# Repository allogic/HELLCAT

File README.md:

# HELLCAT
4-channel DRV8825 stepper motor driver.

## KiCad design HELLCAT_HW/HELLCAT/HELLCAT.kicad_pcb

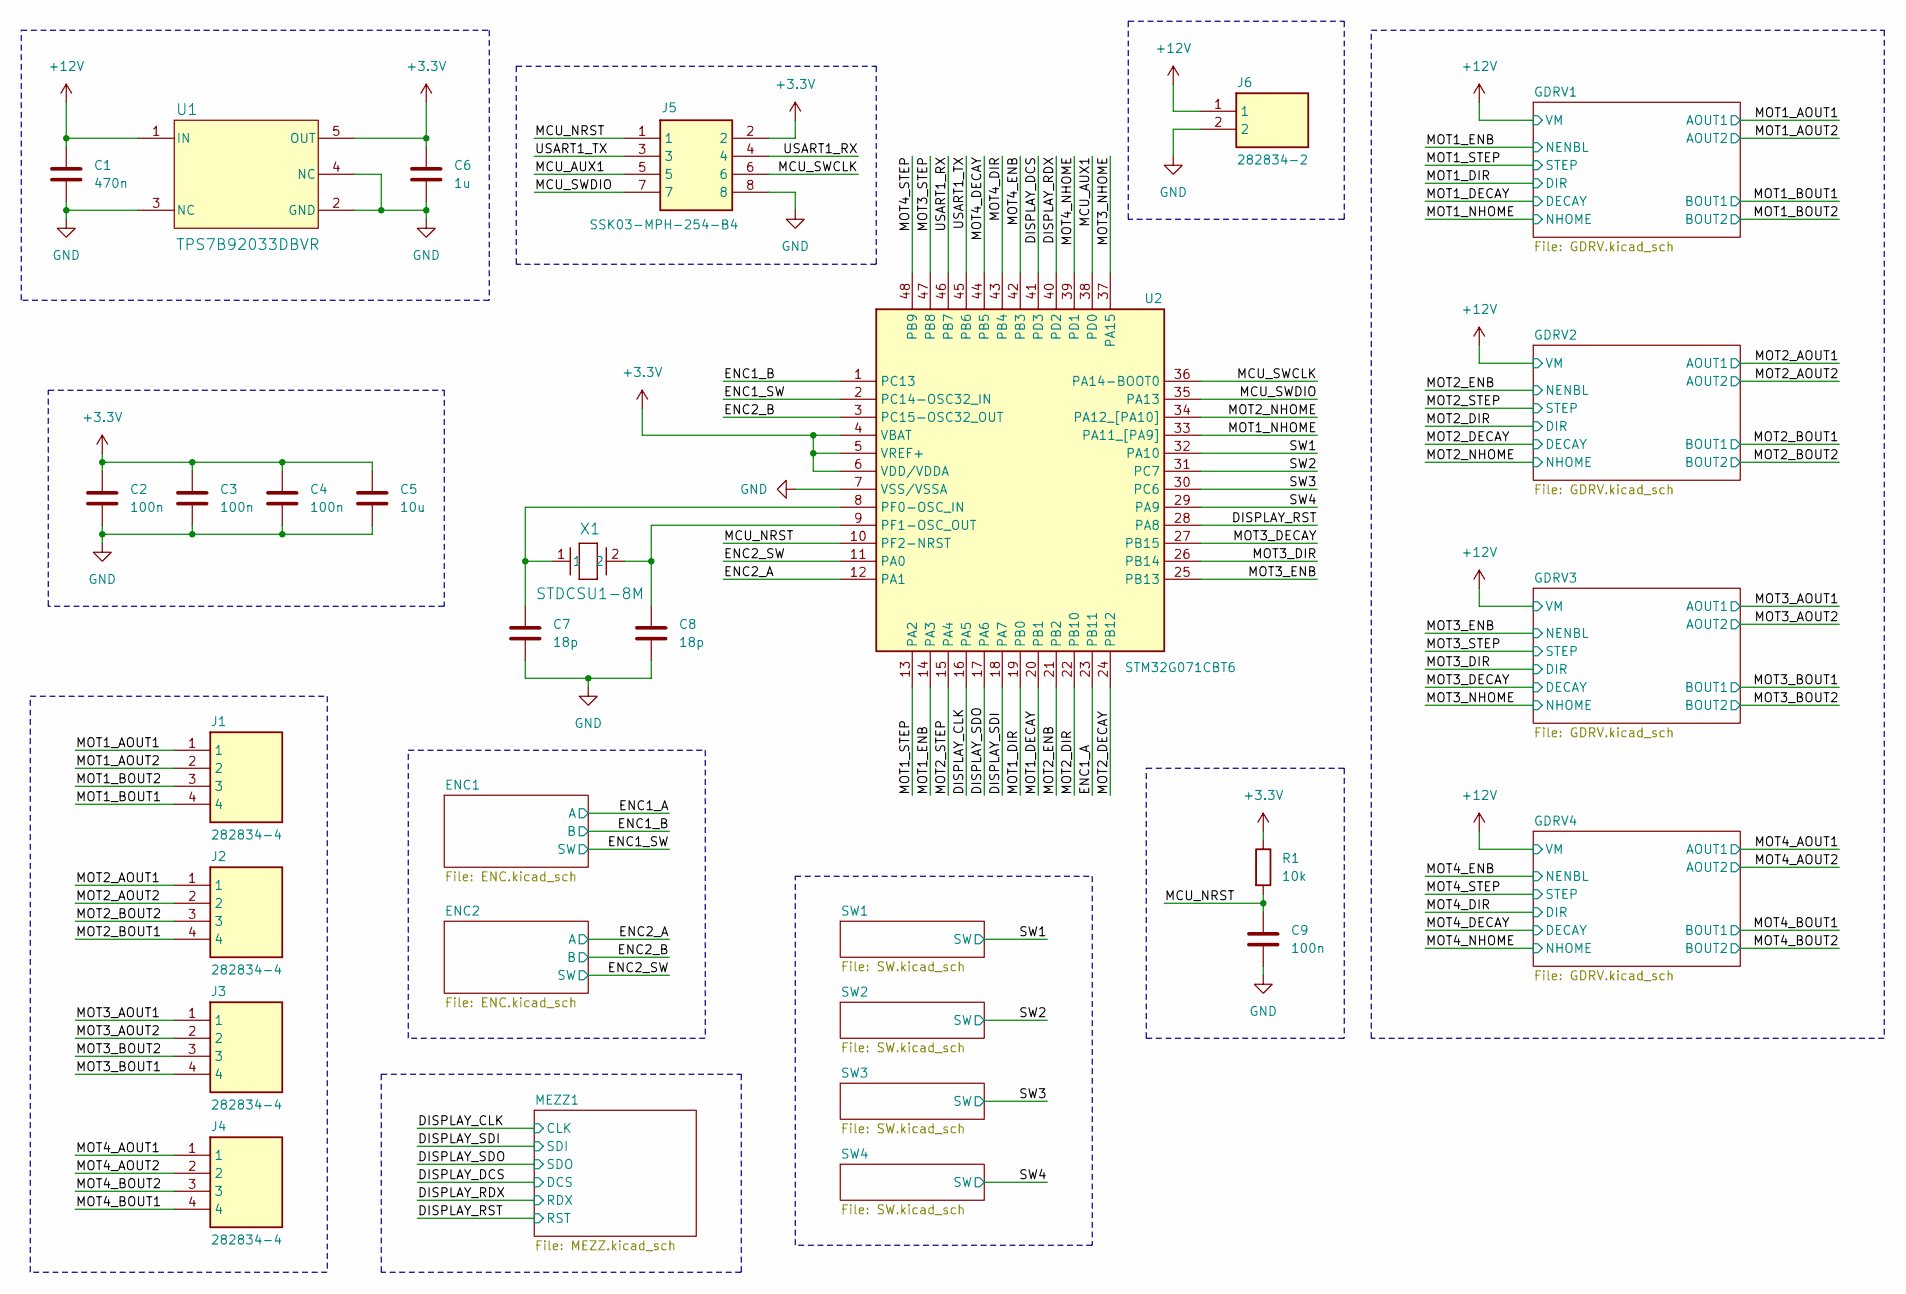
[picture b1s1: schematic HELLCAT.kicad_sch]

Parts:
C1: 470n; C_0603_1608Metric
C2, C3, C4, C9: 100n; C_0603_1608Metric
C5: 10u; C_0603_1608Metric
C6: 1u; C_0603_1608Metric
C7, C8: 18p; C_0603_1608Metric
J1, J2, J3, J4: 282834-4; Manufacturer_Part_Number 282834-4; Mouser Part Number 571-282834-4
J5: SSK03-MPH-254-B4; Manufacturer_Part_Number SSK03-MPH-254-B4
J6: 282834-2; Manufacturer_Part_Number 282834-2; Mouser Part Number 571-282834-2
R1: 10k; R_0603_1608Metric
U1: TPS7B92033DBVR
U2: STM32G071CBT6; Manufacturer_Part_Number STM32G071CBT6; Mouser Part Number 511-STM32G071CBT6
X1: STDCSU1-8M

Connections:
+3.3V: C2.1, C3.1, C4.1, C5.1, C6.1, J5.2, R1.1, U1.5 (OUT), U2.4 (VBAT), U2.5 (VREF+), U2.6 (VDD/VDDA); also elsewhere on the board
+12V: C1.1, J6.1, U1.1 (IN); also elsewhere on the board
/DISPLAY_CLK: U2.16 (PA5); also elsewhere on the board
/DISPLAY_DCS: U2.41 (PD3); also elsewhere on the board
/DISPLAY_RDX: U2.40 (PD2); also elsewhere on the board
/DISPLAY_RST: U2.28 (PA8); also elsewhere on the board
/DISPLAY_SDI: U2.18 (PA7); also elsewhere on the board
/DISPLAY_SDO: U2.17 (PA6); also elsewhere on the board
/ENC1_A: U2.23 (PB11); also elsewhere on the board
/ENC1_B: U2.1 (PC13); also elsewhere on the board
/ENC1_SW: U2.2 (PC14-OSC32_IN); also elsewhere on the board
/ENC2_A: U2.12 (PA1); also elsewhere on the board
/ENC2_B: U2.3 (PC15-OSC32_OUT); also elsewhere on the board
/ENC2_SW: U2.11 (PA0); also elsewhere on the board
/MCU_AUX1: J5.5, U2.38 (PD0)
/MCU_NRST: C9.1, J5.1, R1.2, U2.10 (PF2-NRST)
/MCU_SWCLK: J5.6, U2.36 (PA14-BOOT0)
/MCU_SWDIO: J5.7, U2.35 (PA13)
/MOT1_AOUT1: J1.1; also elsewhere on the board
/MOT1_AOUT2: J1.2; also elsewhere on the board
/MOT1_BOUT1: J1.4; also elsewhere on the board
/MOT1_BOUT2: J1.3; also elsewhere on the board
/MOT1_DECAY: U2.20 (PB1); also elsewhere on the board
/MOT1_DIR: U2.19 (PB0); also elsewhere on the board
/MOT1_ENB: U2.14 (PA3); also elsewhere on the board
/MOT1_NHOME: U2.33 (PA11_[PA9]); also elsewhere on the board
/MOT1_STEP: U2.13 (PA2); also elsewhere on the board
/MOT2_AOUT1: J2.1; also elsewhere on the board
/MOT2_AOUT2: J2.2; also elsewhere on the board
/MOT2_BOUT1: J2.4; also elsewhere on the board
/MOT2_BOUT2: J2.3; also elsewhere on the board
/MOT2_DECAY: U2.24 (PB12); also elsewhere on the board
/MOT2_DIR: U2.22 (PB10); also elsewhere on the board
/MOT2_ENB: U2.21 (PB2); also elsewhere on the board
/MOT2_NHOME: U2.34 (PA12_[PA10]); also elsewhere on the board
/MOT2_STEP: U2.15 (PA4); also elsewhere on the board
/MOT3_AOUT1: J3.1; also elsewhere on the board
/MOT3_AOUT2: J3.2; also elsewhere on the board
/MOT3_BOUT1: J3.4; also elsewhere on the board
/MOT3_BOUT2: J3.3; also elsewhere on the board
/MOT3_DECAY: U2.27 (PB15); also elsewhere on the board
/MOT3_DIR: U2.26 (PB14); also elsewhere on the board
/MOT3_ENB: U2.25 (PB13); also elsewhere on the board
/MOT3_NHOME: U2.37 (PA15); also elsewhere on the board
/MOT3_STEP: U2.47 (PB8); also elsewhere on the board
/MOT4_AOUT1: J4.1; also elsewhere on the board
/MOT4_AOUT2: J4.2; also elsewhere on the board
/MOT4_BOUT1: J4.4; also elsewhere on the board
/MOT4_BOUT2: J4.3; also elsewhere on the board
/MOT4_DECAY: U2.44 (PB5); also elsewhere on the board
/MOT4_DIR: U2.43 (PB4); also elsewhere on the board
/MOT4_ENB: U2.42 (PB3); also elsewhere on the board
/MOT4_NHOME: U2.39 (PD1); also elsewhere on the board
/MOT4_STEP: U2.48 (PB9); also elsewhere on the board
/SW1: U2.32 (PA10); also elsewhere on the board
/SW2: U2.31 (PC7); also elsewhere on the board
/SW3: U2.30 (PC6); also elsewhere on the board
/SW4: U2.29 (PA9); also elsewhere on the board
/USART1_RX: J5.4, U2.46 (PB7)
/USART1_TX: J5.3, U2.45 (PB6)
GND: C1.2, C2.2, C3.2, C4.2, C5.2, C6.2, C7.2, C8.2, C9.2, J5.8, J6.2, U1.2 (GND), U1.3 (NC), U1.4 (NC), U2.7 (VSS/VSSA); also elsewhere on the board
unnamed: C7.1, U2.8 (PF0-OSC_IN), X1.1
unnamed: C8.1, U2.9 (PF1-OSC_OUT), X1.2

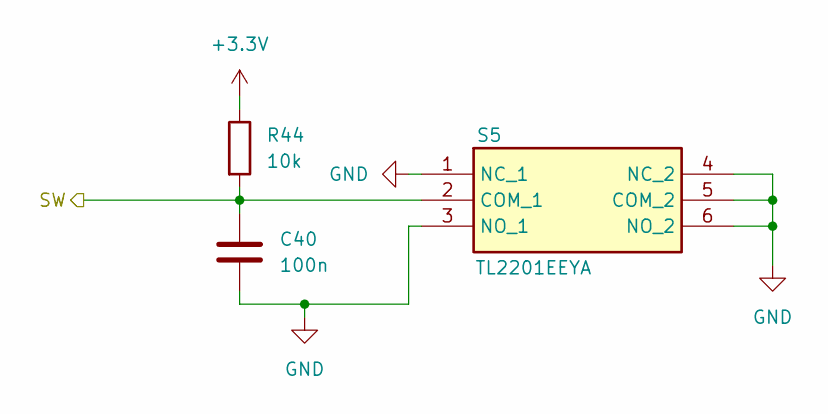
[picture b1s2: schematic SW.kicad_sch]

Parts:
C40: 100n; C_0603_1608Metric
R44: 10k; R_0603_1608Metric
S5: TL2201EEYA; Manufacturer_Part_Number TL2201EEYA; Mouser Part Number 612-TL2201EEYA

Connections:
+3.3V: R44.1; also elsewhere on the board
/SW1: C40.1, R44.2, S5.2 (COM_1); also elsewhere on the board
GND: C40.2, S5.1 (NC_1), S5.3 (NO_1), S5.4 (NC_2), S5.5 (COM_2), S5.6 (NO_2); also elsewhere on the board

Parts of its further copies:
C41, C42, C43: 100n; C_0603_1608Metric
R45, R46, R47: 10k; R_0603_1608Metric
S6, S7, S8: TL2201EEYA; Manufacturer_Part_Number TL2201EEYA; Mouser Part Number 612-TL2201EEYA

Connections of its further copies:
+3.3V: R45.1, R46.1, R47.1; also elsewhere on the board
/SW2: C41.1, R45.2, S6.2 (COM_1); also elsewhere on the board
/SW3: C42.1, R46.2, S7.2 (COM_1); also elsewhere on the board
/SW4: C43.1, R47.2, S8.2 (COM_1); also elsewhere on the board
GND: C41.2, C42.2, C43.2, S6.1 (NC_1), S6.3 (NO_1), S6.4 (NC_2), S6.5 (COM_2), S6.6 (NO_2), S7.1 (NC_1), S7.3 (NO_1), S7.4 (NC_2), S7.5 (COM_2), S7.6 (NO_2), S8.1 (NC_1), S8.3 (NO_1), S8.4 (NC_2), S8.5 (COM_2), S8.6 (NO_2); also elsewhere on the board

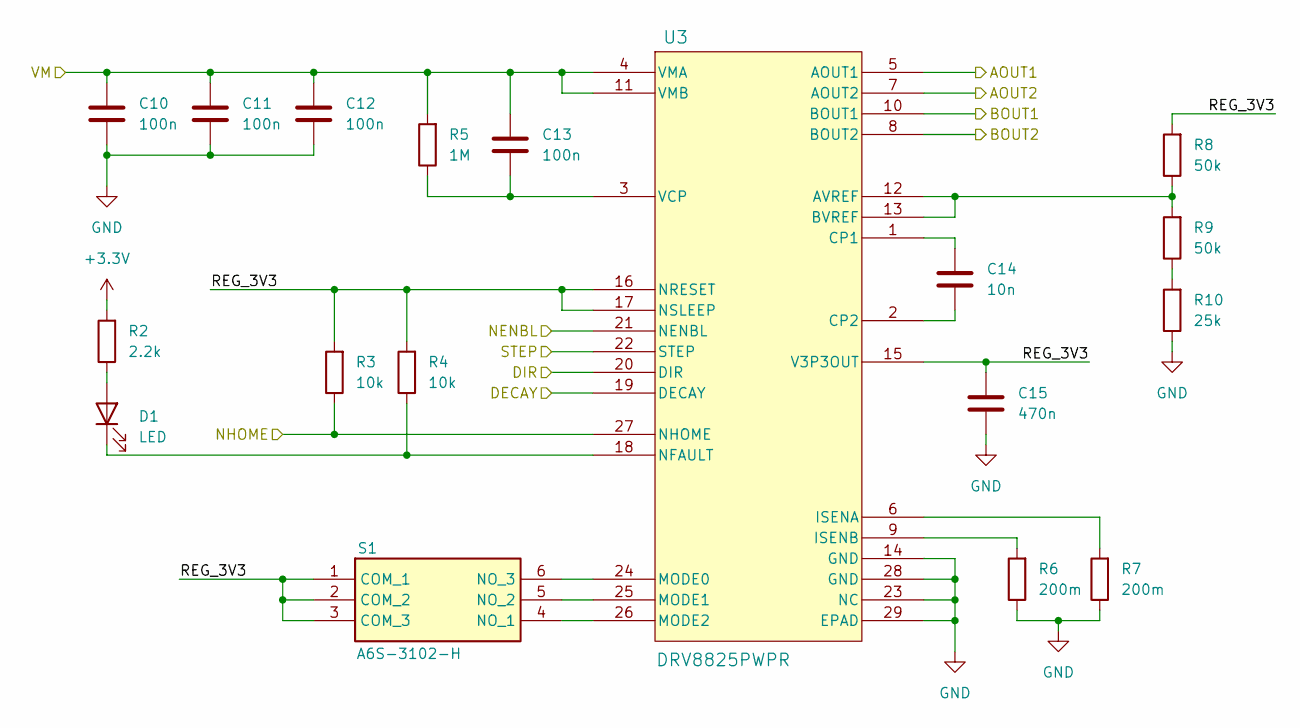
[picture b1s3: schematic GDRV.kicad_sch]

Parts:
C10: 100n; C_1210_3225Metric
C11, C12, C13: 100n; C_0603_1608Metric
C14: 10n; C_0603_1608Metric
C15: 470n; C_0603_1608Metric
D1: LED; LED_0603_1608Metric
R2: 2.2k; R_0603_1608Metric
R3, R4: 10k; R_0603_1608Metric
R5: 1M; R_0603_1608Metric
R6, R7: 200m; R_0603_1608Metric
R8, R9: 50k; R_0603_1608Metric
R10: 25k; R_0603_1608Metric
S1: A6S-3102-H; Manufacturer_Part_Number A6S-3102-H; Mouser Part Number 653-A6S-3102-H
U3: DRV8825PWPR

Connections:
+3.3V: R2.2; also elsewhere on the board
+12V: C10.1, C11.1, C12.1, C13.1, R5.2, U3.4 (VMA), U3.11 (VMB); also elsewhere on the board
/GDRV2/REG_3V3: C15.1, R3.2, R4.2, R8.2, S1.1 (COM_1), S1.2 (COM_2), S1.3 (COM_3), U3.15 (V3P3OUT), U3.16 (NRESET), U3.17 (NSLEEP)
/MOT2_AOUT1: U3.5 (AOUT1); also elsewhere on the board
/MOT2_AOUT2: U3.7 (AOUT2); also elsewhere on the board
/MOT2_BOUT1: U3.10 (BOUT1); also elsewhere on the board
/MOT2_BOUT2: U3.8 (BOUT2); also elsewhere on the board
/MOT2_DECAY: U3.19 (DECAY); also elsewhere on the board
/MOT2_DIR: U3.20 (DIR); also elsewhere on the board
/MOT2_ENB: U3.21 (NENBL); also elsewhere on the board
/MOT2_NHOME: R3.1, U3.27 (NHOME); also elsewhere on the board
/MOT2_STEP: U3.22 (STEP); also elsewhere on the board
GND: C10.2, C11.2, C12.2, C15.2, R6.1, R7.1, R10.1, U3.14 (GND), U3.23 (NC), U3.28 (GND), U3.29 (EPAD); also elsewhere on the board
unnamed: D1.2 (A), R2.1
unnamed: D1.1 (K), R4.1, U3.18 (NFAULT)
unnamed: R9.1, R10.2
unnamed: S1.4 (NO_1), U3.26 (MODE2)
unnamed: S1.5 (NO_2), U3.25 (MODE1)
unnamed: S1.6 (NO_3), U3.24 (MODE0)
unnamed: R8.1, R9.2, U3.12 (AVREF), U3.13 (BVREF)
unnamed: C14.1, U3.1 (CP1)
unnamed: C14.2, U3.2 (CP2)
unnamed: R7.2, U3.6 (ISENA)
unnamed: R6.2, U3.9 (ISENB)
unnamed: C13.2, R5.1, U3.3 (VCP)

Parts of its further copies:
C16, C22, C28: 100n; C_1210_3225Metric
C17, C18, C19, C23, C24, C25, C29, C30, C31: 100n; C_0603_1608Metric
C20, C26, C32: 10n; C_0603_1608Metric
C21, C27, C33: 470n; C_0603_1608Metric
D2, D3, D4: LED; LED_0603_1608Metric
R11, R20, R29: 2.2k; R_0603_1608Metric
R12, R13, R21, R22, R30, R31: 10k; R_0603_1608Metric
R14, R23, R32: 1M; R_0603_1608Metric
R15, R16, R24, R25, R33, R34: 200m; R_0603_1608Metric
R17, R18, R26, R27, R35, R36: 50k; R_0603_1608Metric
R19, R28, R37: 25k; R_0603_1608Metric
S2, S3, S4: A6S-3102-H; Manufacturer_Part_Number A6S-3102-H; Mouser Part Number 653-A6S-3102-H
U4, U5, U6: DRV8825PWPR

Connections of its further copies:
+3.3V: R11.2, R20.2, R29.2; also elsewhere on the board
+12V: C16.1, C17.1, C18.1, C19.1, C22.1, C23.1, C24.1, C25.1, C28.1, C29.1, C30.1, C31.1, R14.2, R23.2, R32.2, U4.4 (VMA), U4.11 (VMB), U5.4 (VMA), U5.11 (VMB), U6.4 (VMA), U6.11 (VMB); also elsewhere on the board
/GDRV1/REG_3V3: C21.1, R12.2, R13.2, R17.2, S2.1 (COM_1), S2.2 (COM_2), S2.3 (COM_3), U4.15 (V3P3OUT), U4.16 (NRESET), U4.17 (NSLEEP)
/GDRV3/REG_3V3: C27.1, R21.2, R22.2, R26.2, S3.1 (COM_1), S3.2 (COM_2), S3.3 (COM_3), U5.15 (V3P3OUT), U5.16 (NRESET), U5.17 (NSLEEP)
/GDRV4/REG_3V3: C33.1, R30.2, R31.2, R35.2, S4.1 (COM_1), S4.2 (COM_2), S4.3 (COM_3), U6.15 (V3P3OUT), U6.16 (NRESET), U6.17 (NSLEEP)
/MOT1_AOUT1: U4.5 (AOUT1); also elsewhere on the board
/MOT1_AOUT2: U4.7 (AOUT2); also elsewhere on the board
/MOT1_BOUT1: U4.10 (BOUT1); also elsewhere on the board
/MOT1_BOUT2: U4.8 (BOUT2); also elsewhere on the board
/MOT1_DECAY: U4.19 (DECAY); also elsewhere on the board
/MOT1_DIR: U4.20 (DIR); also elsewhere on the board
/MOT1_ENB: U4.21 (NENBL); also elsewhere on the board
/MOT1_NHOME: R12.1, U4.27 (NHOME); also elsewhere on the board
/MOT1_STEP: U4.22 (STEP); also elsewhere on the board
/MOT3_AOUT1: U5.5 (AOUT1); also elsewhere on the board
/MOT3_AOUT2: U5.7 (AOUT2); also elsewhere on the board
/MOT3_BOUT1: U5.10 (BOUT1); also elsewhere on the board
/MOT3_BOUT2: U5.8 (BOUT2); also elsewhere on the board
/MOT3_DECAY: U5.19 (DECAY); also elsewhere on the board
/MOT3_DIR: U5.20 (DIR); also elsewhere on the board
/MOT3_ENB: U5.21 (NENBL); also elsewhere on the board
/MOT3_NHOME: R21.1, U5.27 (NHOME); also elsewhere on the board
/MOT3_STEP: U5.22 (STEP); also elsewhere on the board
/MOT4_AOUT1: U6.5 (AOUT1); also elsewhere on the board
/MOT4_AOUT2: U6.7 (AOUT2); also elsewhere on the board
/MOT4_BOUT1: U6.10 (BOUT1); also elsewhere on the board
/MOT4_BOUT2: U6.8 (BOUT2); also elsewhere on the board
/MOT4_DECAY: U6.19 (DECAY); also elsewhere on the board
/MOT4_DIR: U6.20 (DIR); also elsewhere on the board
/MOT4_ENB: U6.21 (NENBL); also elsewhere on the board
/MOT4_NHOME: R30.1, U6.27 (NHOME); also elsewhere on the board
/MOT4_STEP: U6.22 (STEP); also elsewhere on the board
GND: C16.2, C17.2, C18.2, C21.2, C22.2, C23.2, C24.2, C27.2, C28.2, C29.2, C30.2, C33.2, R15.1, R16.1, R19.1, R24.1, R25.1, R28.1, R33.1, R34.1, R37.1, U4.14 (GND), U4.23 (NC), U4.28 (GND), U4.29 (EPAD), U5.14 (GND), U5.23 (NC), U5.28 (GND), U5.29 (EPAD), U6.14 (GND), U6.23 (NC), U6.28 (GND), U6.29 (EPAD); also elsewhere on the board
unnamed: D2.2 (A), R11.1
unnamed: D2.1 (K), R13.1, U4.18 (NFAULT)
unnamed: D3.2 (A), R20.1
unnamed: D3.1 (K), R22.1, U5.18 (NFAULT)
unnamed: D4.2 (A), R29.1
unnamed: D4.1 (K), R31.1, U6.18 (NFAULT)
unnamed: R18.1, R19.2
unnamed: R27.1, R28.2
unnamed: R36.1, R37.2
unnamed: S2.4 (NO_1), U4.26 (MODE2)
unnamed: S2.5 (NO_2), U4.25 (MODE1)
unnamed: S2.6 (NO_3), U4.24 (MODE0)
unnamed: S3.4 (NO_1), U5.26 (MODE2)
unnamed: S3.5 (NO_2), U5.25 (MODE1)
unnamed: S3.6 (NO_3), U5.24 (MODE0)
unnamed: S4.4 (NO_1), U6.26 (MODE2)
unnamed: S4.5 (NO_2), U6.25 (MODE1)
unnamed: S4.6 (NO_3), U6.24 (MODE0)
unnamed: R17.1, R18.2, U4.12 (AVREF), U4.13 (BVREF)
unnamed: C20.1, U4.1 (CP1)
unnamed: C20.2, U4.2 (CP2)
unnamed: R16.2, U4.6 (ISENA)
unnamed: R15.2, U4.9 (ISENB)
unnamed: C19.2, R14.1, U4.3 (VCP)
unnamed: R26.1, R27.2, U5.12 (AVREF), U5.13 (BVREF)
unnamed: C26.1, U5.1 (CP1)
unnamed: C26.2, U5.2 (CP2)
unnamed: R25.2, U5.6 (ISENA)
unnamed: R24.2, U5.9 (ISENB)
unnamed: C25.2, R23.1, U5.3 (VCP)
unnamed: R35.1, R36.2, U6.12 (AVREF), U6.13 (BVREF)
unnamed: C32.1, U6.1 (CP1)
unnamed: C32.2, U6.2 (CP2)
unnamed: R34.2, U6.6 (ISENA)
unnamed: R33.2, U6.9 (ISENB)
unnamed: C31.2, R32.1, U6.3 (VCP)

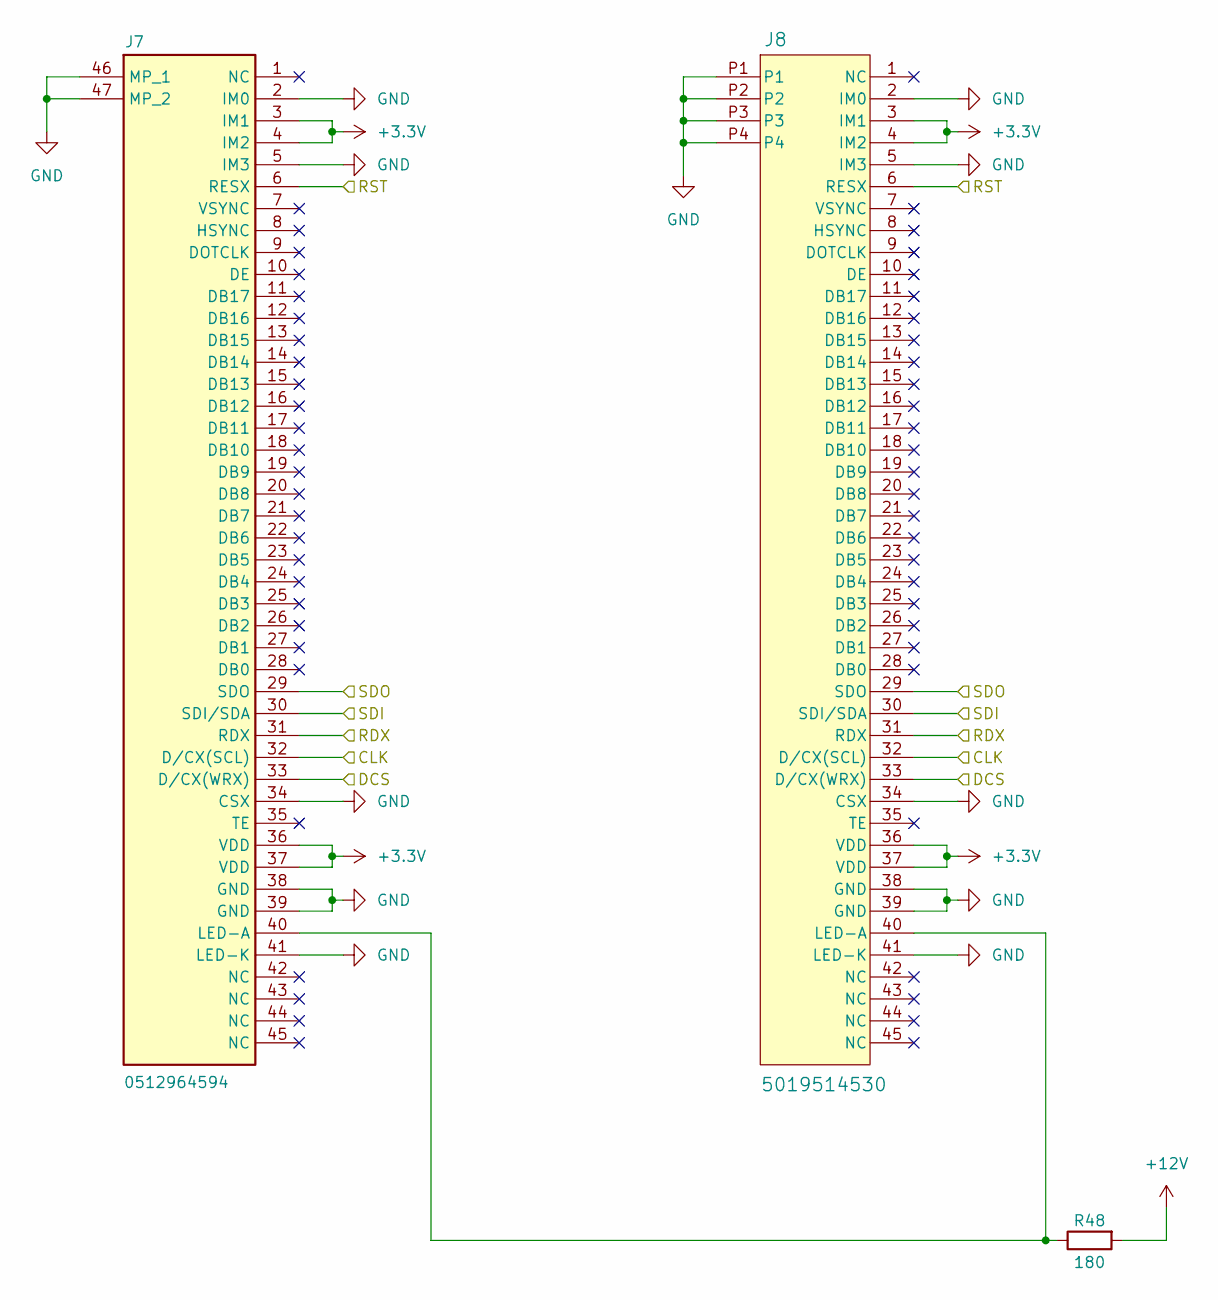
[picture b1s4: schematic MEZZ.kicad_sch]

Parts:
J7: 0512964594; Manufacturer_Part_Number 0512964594
J8: 5019514530
R48: 180; R_0603_1608Metric

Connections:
+3.3V: J7.3 (IM1), J7.4 (IM2), J7.36 (VDD), J7.37 (VDD), J8.3 (IM1), J8.4 (IM2), J8.36 (VDD), J8.37 (VDD); also elsewhere on the board
+12V: R48.2; also elsewhere on the board
/DISPLAY_CLK: J7.32 (D/CX(SCL)), J8.32 (D/CX(SCL)); also elsewhere on the board
/DISPLAY_DCS: J7.33 (D/CX(WRX)), J8.33 (D/CX(WRX)); also elsewhere on the board
/DISPLAY_RDX: J7.31 (RDX), J8.31 (RDX); also elsewhere on the board
/DISPLAY_RST: J7.6 (RESX), J8.6 (RESX); also elsewhere on the board
/DISPLAY_SDI: J7.30 (SDI/SDA), J8.30 (SDI/SDA); also elsewhere on the board
/DISPLAY_SDO: J7.29 (SDO), J8.29 (SDO); also elsewhere on the board
GND: J7.2 (IM0), J7.5 (IM3), J7.34 (CSX), J7.38 (GND), J7.39 (GND), J7.41 (LED-K), J7.46 (MP_1), J7.47 (MP_2), J8.2 (IM0), J8.5 (IM3), J8.34 (CSX), J8.38 (GND), J8.39 (GND), J8.41 (LED-K), J8.P1, J8.P2, J8.P3, J8.P4; also elsewhere on the board
unnamed: J7.40 (LED-A), J8.40 (LED-A), R48.1

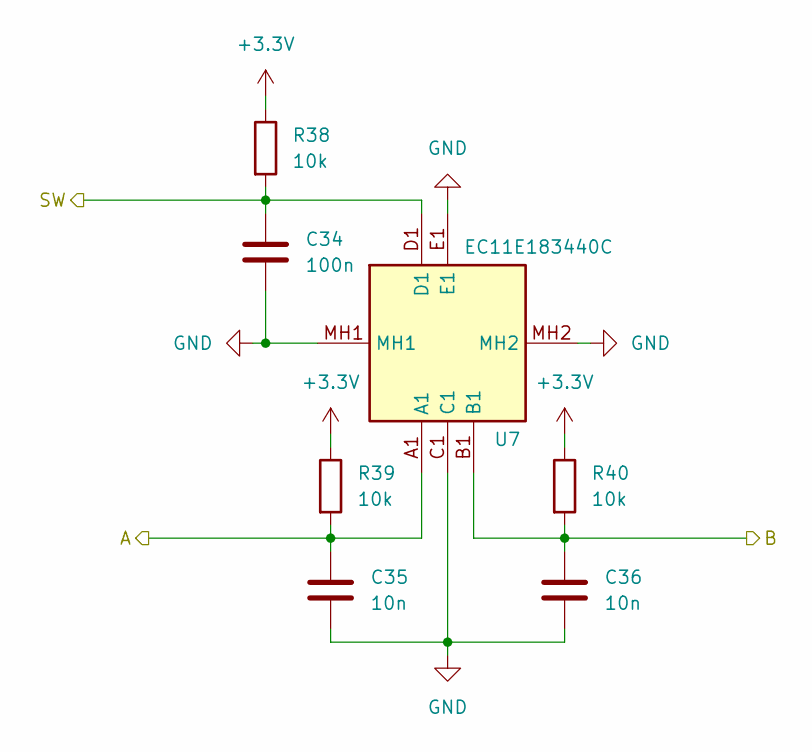
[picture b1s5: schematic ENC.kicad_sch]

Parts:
C34: 100n; C_0603_1608Metric
C35, C36: 10n; C_0603_1608Metric
R38, R39, R40: 10k; R_0603_1608Metric
U7: EC11E183440C; Manufacturer_Part_Number EC11E183440C; Mouser Part Number 688-EC11E183440C

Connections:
+3.3V: R38.1, R39.1, R40.1; also elsewhere on the board
/ENC1_A: C35.1, R39.2, U7.A1; also elsewhere on the board
/ENC1_B: C36.1, R40.2, U7.B1; also elsewhere on the board
/ENC1_SW: C34.1, R38.2, U7.D1; also elsewhere on the board
GND: C34.2, C35.2, C36.2, U7.C1, U7.E1, U7.MH1, U7.MH2; also elsewhere on the board

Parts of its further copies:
C37: 100n; C_0603_1608Metric
C38, C39: 10n; C_0603_1608Metric
R41, R42, R43: 10k; R_0603_1608Metric
U8: EC11E183440C; Manufacturer_Part_Number EC11E183440C; Mouser Part Number 688-EC11E183440C

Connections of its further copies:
+3.3V: R41.1, R42.1, R43.1; also elsewhere on the board
/ENC2_A: C38.1, R42.2, U8.A1; also elsewhere on the board
/ENC2_B: C39.1, R43.2, U8.B1; also elsewhere on the board
/ENC2_SW: C37.1, R41.2, U8.D1; also elsewhere on the board
GND: C37.2, C38.2, C39.2, U8.C1, U8.E1, U8.MH1, U8.MH2; also elsewhere on the board

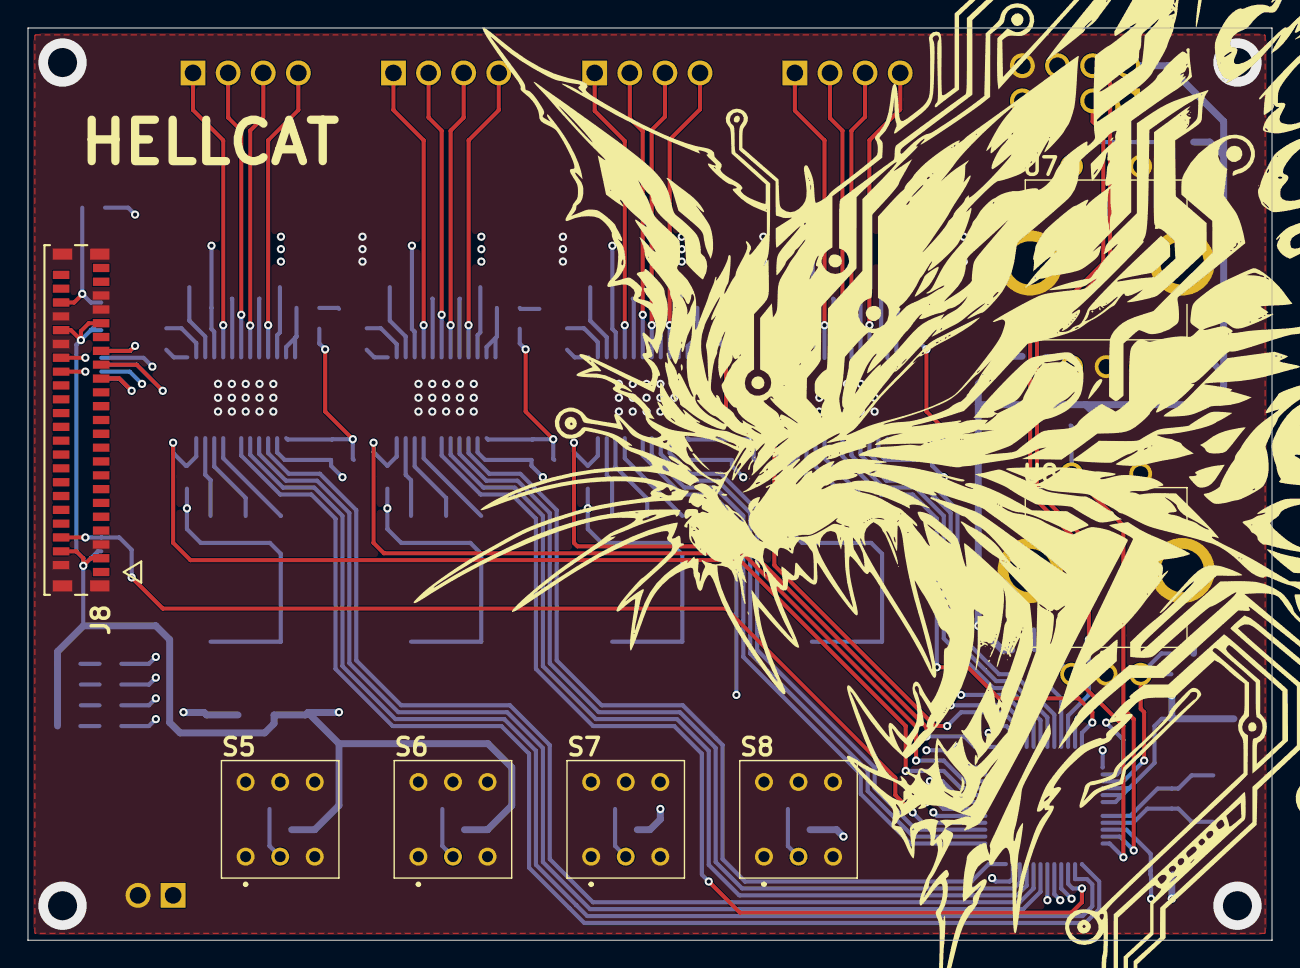
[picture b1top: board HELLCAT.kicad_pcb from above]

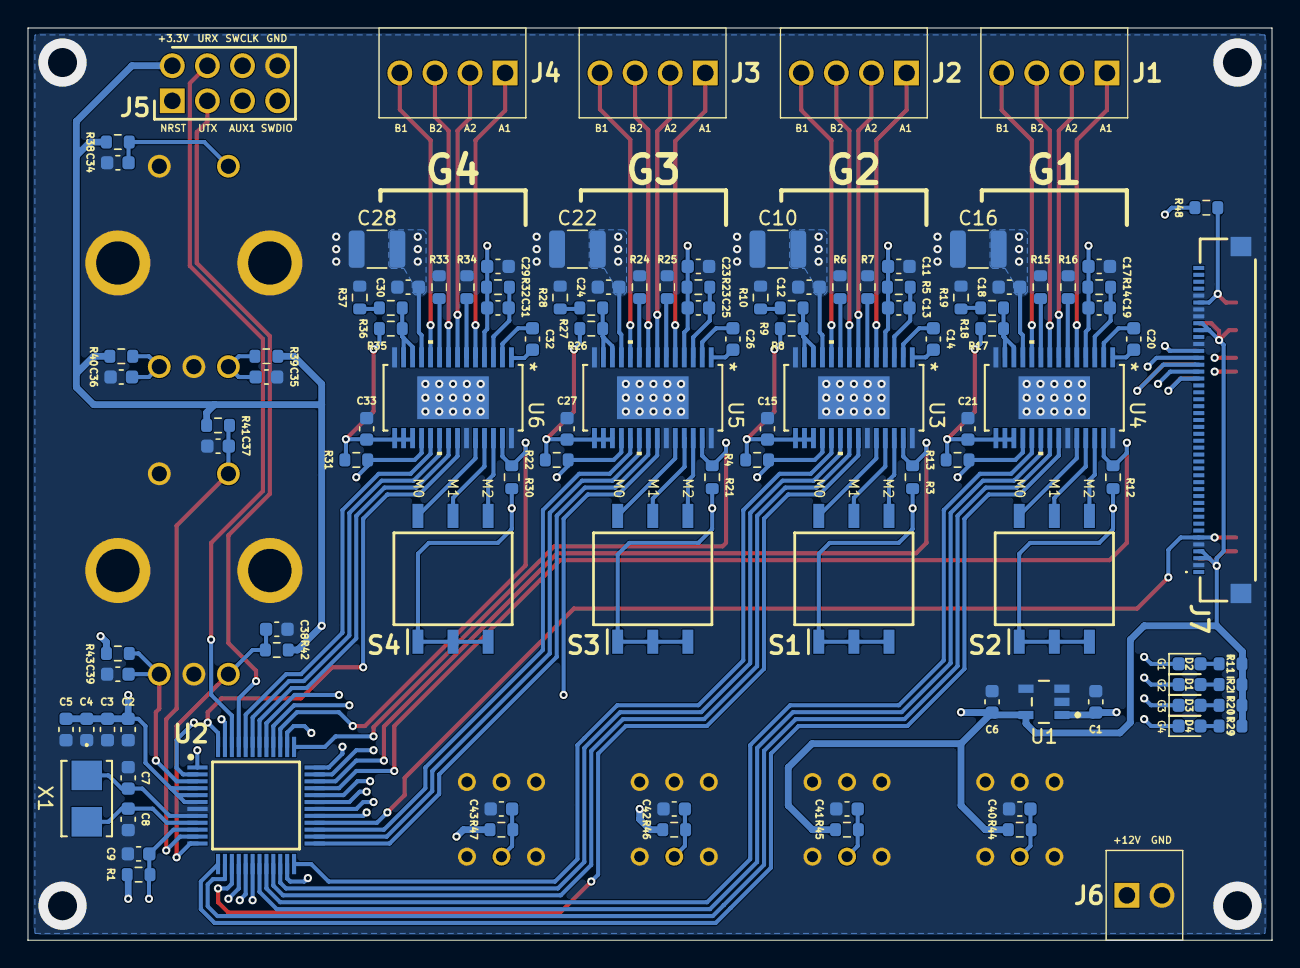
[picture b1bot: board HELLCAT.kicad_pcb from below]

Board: 4 copper layers, 90.0 x 66.0 mm, 120 parts (113 on the bottom side), 116 nets.
